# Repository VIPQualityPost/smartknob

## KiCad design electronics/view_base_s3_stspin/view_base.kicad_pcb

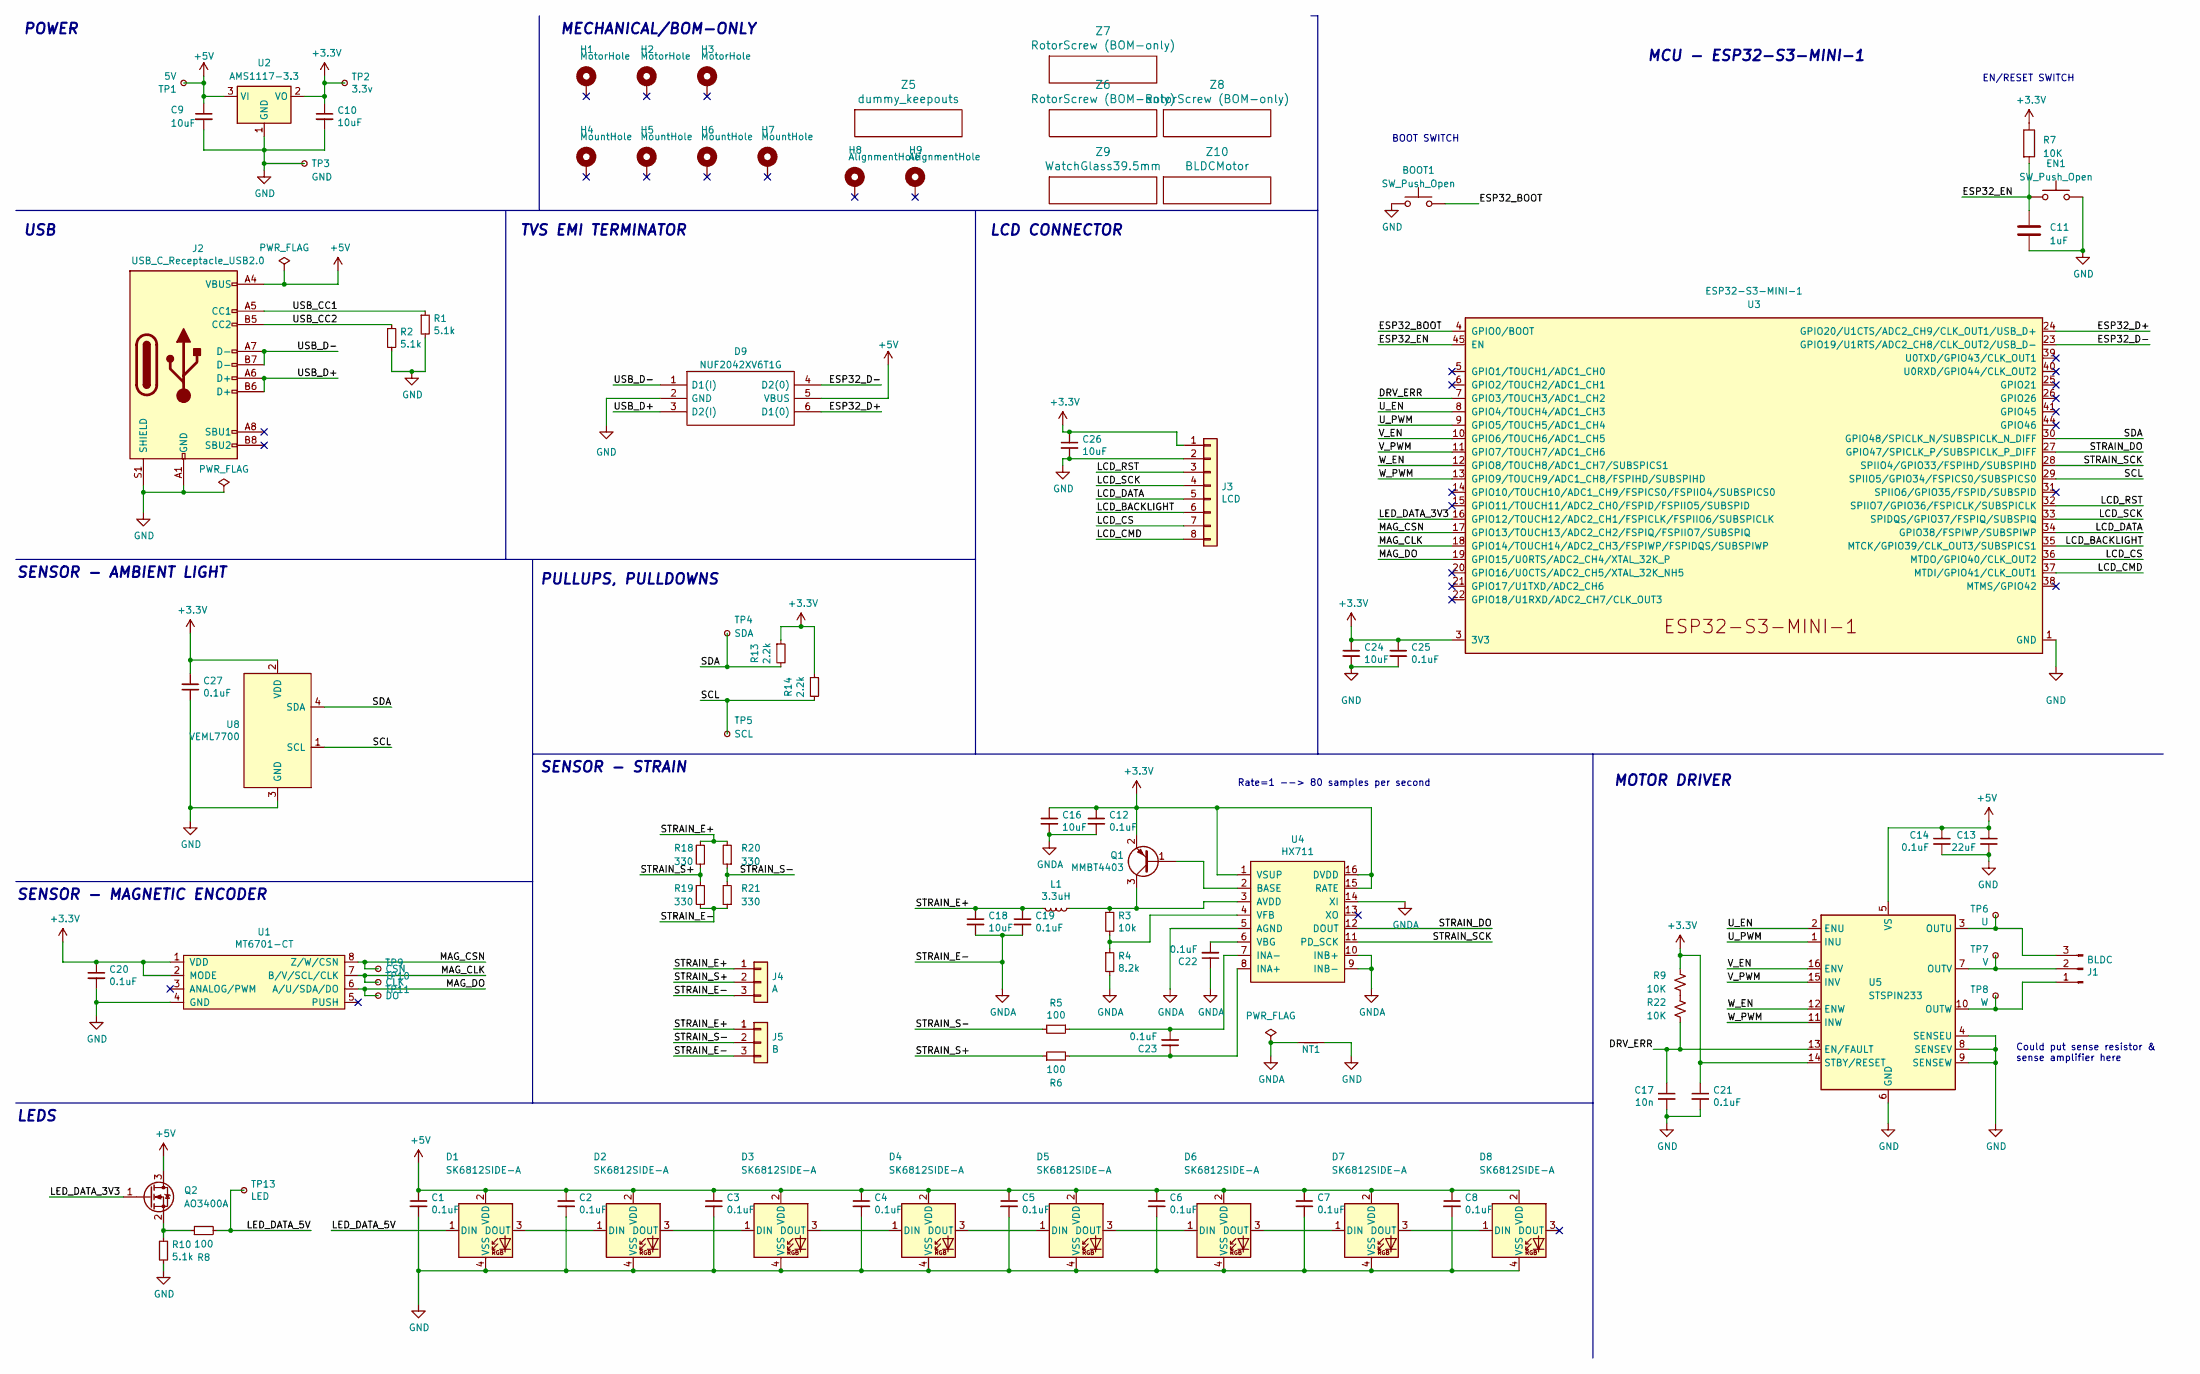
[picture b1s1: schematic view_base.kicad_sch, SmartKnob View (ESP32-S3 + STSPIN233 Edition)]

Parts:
BOOT1: SW_Push_Open; SW_Push_SPST_NO_Alps_SKRK
C1, C2, C3, C4, C5, C6, C7, C8, C12, C14, C19, C20, C21, C22, C23, C25, C27: 0.1uF; C_0603_1608Metric; LCSC C1591
C9, C10, C16, C18, C24, C26: 10uF; C_0805_2012Metric; LCSC C2922480
C11: 1uF; C_0603_1608Metric
C13: 22uF; C_0805_2012Metric; LCSC C98190
C17: 10n; C_0603_1608Metric; LCSC C1591
D1, D2, D3, D4, D5, D6, D7, D8: SK6812SIDE-A; SK6812-SIDE-A; Digikey 1528-4691-ND
D9: NUF2042XV6T1G; SOT-563; Mouser Part Number 863-NUF2042XV6T1G
EN1: SW_Push_Open; SW_Push_SPST_NO_Alps_SKRK
H1, H2, H3: MotorHole; MountingHole_M1.6; LCSC C2931389
H4, H5, H6, H7: MountHole; MountingHole_2.2mm_M2_ISO7380_Pad_NonVirtual; LCSC C2911210 or C2911532 (screw), C2961595 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
H8, H9: AlignmentHole; MountingHole_2.2mm_M2_ISO7380_Pad_NonVirtual
J1: BLDC; 532610371; LCSC C293630
J2: USB_C_Receptacle_USB2.0; USB4510_NoPaste; LCSC C428463
J3: LCD; SolderPads_2mm_8
J4: A; SolderPads_2mm_3_STRAIN
J5: B; SolderPads_2mm_3_STRAIN
L1: 3.3uH; L_0805_2012Metric; LCSC C307744
NT1: NetTie_2; NetTie-2_SMD_Pad0.5mm
Q1: MMBT4403; SOT-23; LCSC C78864
Q2: AO3400A; SOT-23
R1, R2, R10: 5.1k; R_0603_1608Metric; LCSC C105580
R3: 10k; R_0603_1608Metric; LCSC C98220
R4: 8.2k; R_0603_1608Metric; LCSC C114637
R5, R6, R8: 100; R_0603_1608Metric; LCSC C319953
R7, R9, R22: 10K; R_0603_1608Metric
R13, R14: 2.2k; R_0603_1608Metric; LCSC C4190
R18, R19, R20, R21: 330; R_2512_6332Metric; LCSC C19866
TP1: 5V; TestPoint_Pad_D2.0mm_ValueSilk
TP2: 3.3v; TestPoint_Pad_D2.0mm_ValueSilk
TP3: GND; TestPoint_Pad_D2.0mm_ValueSilk
TP4: SDA; TestPoint_Pad_D2.0mm_ValueSilk
TP5: SCL; TestPoint_Pad_D2.0mm_ValueSilk
TP6: U; TestPoint_Pad_D2.0mm_ValueSilk
TP7: V; TestPoint_Pad_D2.0mm_ValueSilk
TP8: W; TestPoint_Pad_D2.0mm_ValueSilk
TP9: CSN; TestPoint_Pad_D2.0mm_ValueSilk
TP10: CLK; TestPoint_Pad_D2.0mm_ValueSilk
TP11: DO; TestPoint_Pad_D2.0mm_ValueSilk
TP13: LED; TestPoint_Pad_D2.0mm_ValueSilk
U1: MT6701-CT; SOIC-8_3.9x4.9mm_P1.27mm; LCSC C2856764, or C3003196
U2: AMS1117-3.3; SOT-223-3_TabPin2; LCSC C5120765
U3: ESP32-S3-MINI-1
U4: HX711; SOIC-16_3.9x9.9mm_P1.27mm; LCSC C43656
U5: STSPIN233; VQFN-16-1EP_3x3mm_P0.5mm_EP1.8x1.8mm
U8: VEML7700; VEML7700-TOP; Digikey VEML7700-TT
Z5: dummy_keepouts; ViewKeepouts3d
Z6, Z7, Z8: RotorScrew (BOM-only); bom_only_no_pin
Z9: WatchGlass39.5mm; bom_only_no_pin
Z10: BLDCMotor; bom_only_no_pin

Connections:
+3V3: C10.1, C12.1, C16.1, C20.1, C21.1, C24.1, C25.1, C26.1, C27.1, J3.1, Q1.2 (E), R7.1, R9.1, R13.1, R14.1, TP2.1, U1.1 (VDD), U1.2 (MODE), U2.2 (VO), U3.3 (3V3), U4.1 (VSUP), U4.15 (RATE), U4.16 (DVDD), U5.14 (STBY/RESET), U8.2 (VDD)
+5V: C1.1, C2.1, C3.1, C4.1, C5.1, C6.1, C7.1, C8.1, C9.1, C13.1, C14.1, D1.2 (VDD), D2.2 (VDD), D3.2 (VDD), D4.2 (VDD), D5.2 (VDD), D6.2 (VDD), D7.2 (VDD), D8.2 (VDD), D9.5 (VBUS), J2.A4 (VBUS), J2.A9 (VBUS), J2.B4 (VBUS), J2.B9 (VBUS), Q2.3 (D), TP1.1, U2.3 (VI), U5.5 (VS)
/DRV_ERR: C17.1, R22.2, U3.7 (GPIO3/TOUCH3/ADC1_CH2), U5.13 (EN/FAULT)
/ESP32_BOOT: BOOT1.2, U3.4 (GPIO0/BOOT); also elsewhere on the board
/ESP32_D+: D9.6 (D1(0)), U3.24 (GPIO20/U1CTS/ADC2_CH9/CLK_OUT1/USB_D+)
/ESP32_D-: D9.4 (D2(0)), U3.23 (GPIO19/U1RTS/ADC2_CH8/CLK_OUT2/USB_D-)
/ESP32_EN: C11.1, EN1.1, R7.2, U3.45 (EN); also elsewhere on the board
/LCD_BACKLIGHT: J3.6, U3.35 (MTCK/GPIO39/CLK_OUT3/SUBSPICS1)
/LCD_CMD: J3.8, U3.37 (MTDI/GPIO41/CLK_OUT1)
/LCD_CS: J3.7, U3.36 (MTDO/GPIO40/CLK_OUT2)
/LCD_DATA: J3.5, U3.34 (GPIO38/FSPIWP/SUBSPIWP)
/LCD_RST: J3.3, U3.32 (SPIIO7/GPIO36/FSPICLK/SUBSPICLK)
/LCD_SCK: J3.4, U3.33 (SPIDQS/GPIO37/FSPIQ/SUBSPIQ)
/LED_DATA_3V3: Q2.1 (G), U3.16 (GPIO12/TOUCH12/ADC2_CH1/FSPICLK/FSPIIO6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)
/LED_DATA_5V: D1.1 (DIN), R8.2, TP13.1
/MAG_CLK: TP10.1, U1.7 (B/V/SCL/CLK), U3.18 (GPIO14/TOUCH14/ADC2_CH3/FSPIWP/FSPIDQS/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)
/MAG_CSN: TP9.1, U1.8 (Z/W/CSN), U3.17 (GPIO13/TOUCH13/ADC2_CH2/FSPIQ/FSPIIO7/S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)
/MAG_DO: TP11.1, U1.6 (A/U/SDA/DO), U3.19 (GPIO15/U0RTS/ADC2_CH4/XTAL_32K_P)
/SCL: R14.2, TP5.1, U3.29 (SPIIO5/GPIO34/FSPICS0/SUBSPICS0), U8.1 (SCL)
/SDA: R13.2, TP4.1, U3.30 (GPIO48/SPICLK_N/SUBSPICLK_N_DIFF), U8.4 (SDA)
/STRAIN_DO: U3.27 (GPIO47/SPICLK_P/SUBSPICLK_P_DIFF), U4.12 (DOUT)
/STRAIN_E+: C18.1, C19.1, J4.1, J5.1, L1.2, R18.1, R20.2
/STRAIN_S+: J4.2, R6.1, R18.2, R19.1
/STRAIN_S-: J5.2, R5.2, R20.1, R21.2
/STRAIN_SCK: U3.28 (SPIIO4/GPIO33/FSPIHD/SUBSPIHD), U4.11 (PD_SCK)
/USB_CC1: J2.A5 (CC1), R1.1
/USB_CC2: J2.B5 (CC2), R2.1
/USB_D+: D9.3 (D2(I)), J2.A6 (D+), J2.B6 (D+)
/USB_D-: D9.1 (D1(I)), J2.A7 (D-), J2.B7 (D-)
/U_EN: U3.8 (GPIO4/TOUCH4/ADC1_CH3), U5.2 (ENU); also elsewhere on the board
/U_PWM: U3.9 (GPIO5/TOUCH5/ADC1_CH4), U5.1 (INU); also elsewhere on the board
/V_EN: U3.10 (GPIO6/TOUCH6/ADC1_CH5), U5.16 (ENV); also elsewhere on the board
/V_PWM: U3.11 (GPIO7/TOUCH7/ADC1_CH6), U5.15 (INV); also elsewhere on the board
/W_EN: U3.12 (GPIO8/TOUCH8/ADC1_CH7/SUBSPICS1), U5.12 (ENW); also elsewhere on the board
/W_PWM: U3.13 (GPIO9/TOUCH9/ADC1_CH8/FSPIHD/SUBSPIHD), U5.11 (INW); also elsewhere on the board
GND: BOOT1.1, C1.2, C2.2, C3.2, C4.2, C5.2, C6.2, C7.2, C8.2, C9.2, C10.2, C11.2, C13.2, C14.2, C17.2, C20.2, C21.2, C24.2, C25.2, C26.2, C27.2, D1.4 (VSS), D2.4 (VSS), D3.4 (VSS), D4.4 (VSS), D5.4 (VSS), D6.4 (VSS), D7.4 (VSS), D8.4 (VSS), D9.2 (GND), EN1.2, J2.A1 (GND), J2.A12 (GND), J2.B1 (GND), J2.B12 (GND), J2.S1 (SHIELD), J3.2, NT1.2, R1.2, R2.2, R10.2, TP3.1, U1.4 (GND), U2.1 (GND), U3.1 (GND), U3.2 (GND), U3.42 (GND), U3.43 (GND), U3.46 (GND), U3.47 (GND), U3.48 (GND), U3.49 (GND), U3.50 (GND), U3.51 (GND), U3.52 (GND), U3.53 (GND), U3.54 (GND), U3.55 (GND), U3.56 (GND), U3.57 (GND), U3.58 (GND), U3.59 (GND), U3.60 (GND), U3.61 (GND), U3.62 (GND), U3.63 (GND), U3.64 (GND), U3.65 (GND), U5.4 (SENSEU), U5.6 (GND), U5.8 (SENSEV), U5.9 (SENSEW), U5.17 (GND), U8.3 (GND); also elsewhere on the board
GNDA: C12.2, C16.2, C18.2, C19.2, C22.1, J4.3, J5.3, NT1.1, R4.2, R19.2, R21.1, U4.5 (AGND), U4.9 (INB-), U4.10 (INB+), U4.14 (XI)
unnamed: D1.3 (DOUT), D2.1 (DIN)
unnamed: D2.3 (DOUT), D3.1 (DIN)
unnamed: D3.3 (DOUT), D4.1 (DIN)
unnamed: D4.3 (DOUT), D5.1 (DIN)
unnamed: D5.3 (DOUT), D6.1 (DIN)
unnamed: D6.3 (DOUT), D7.1 (DIN)
unnamed: D7.3 (DOUT), D8.1 (DIN)
unnamed: J1.1, TP8.1, U5.10 (OUTW)
unnamed: J1.2, TP7.1, U5.7 (OUTV)
unnamed: J1.3, TP6.1, U5.3 (OUTU)
unnamed: Q1.1 (B), U4.2 (BASE)
unnamed: L1.1, Q1.3 (C), R3.1, U4.3 (AVDD)
unnamed: Q2.2 (S), R8.1, R10.1
unnamed: R9.2, R22.1
unnamed: C23.1, R6.2, U4.8 (INA+)
unnamed: C23.2, R5.1, U4.7 (INA-)
unnamed: C22.2, U4.6 (VBG)
unnamed: R3.2, R4.1, U4.4 (VFB)

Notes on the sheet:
POWER
Could put sense resistor & sense amplifier here
MCU - ESP32-S3-MINI-1
SENSOR - MAGNETIC ENCODER
MOTOR DRIVER
MECHANICAL/BOM-ONLY
TVS EMI TERMINATOR
Rate=1 --> 80 samples per second
EN/RESET SWITCH
SENSOR - AMBIENT LIGHT
BOOT SWITCH
USB
SENSOR - STRAIN
LEDS
PULLUPS, PULLDOWNS
LCD CONNECTOR

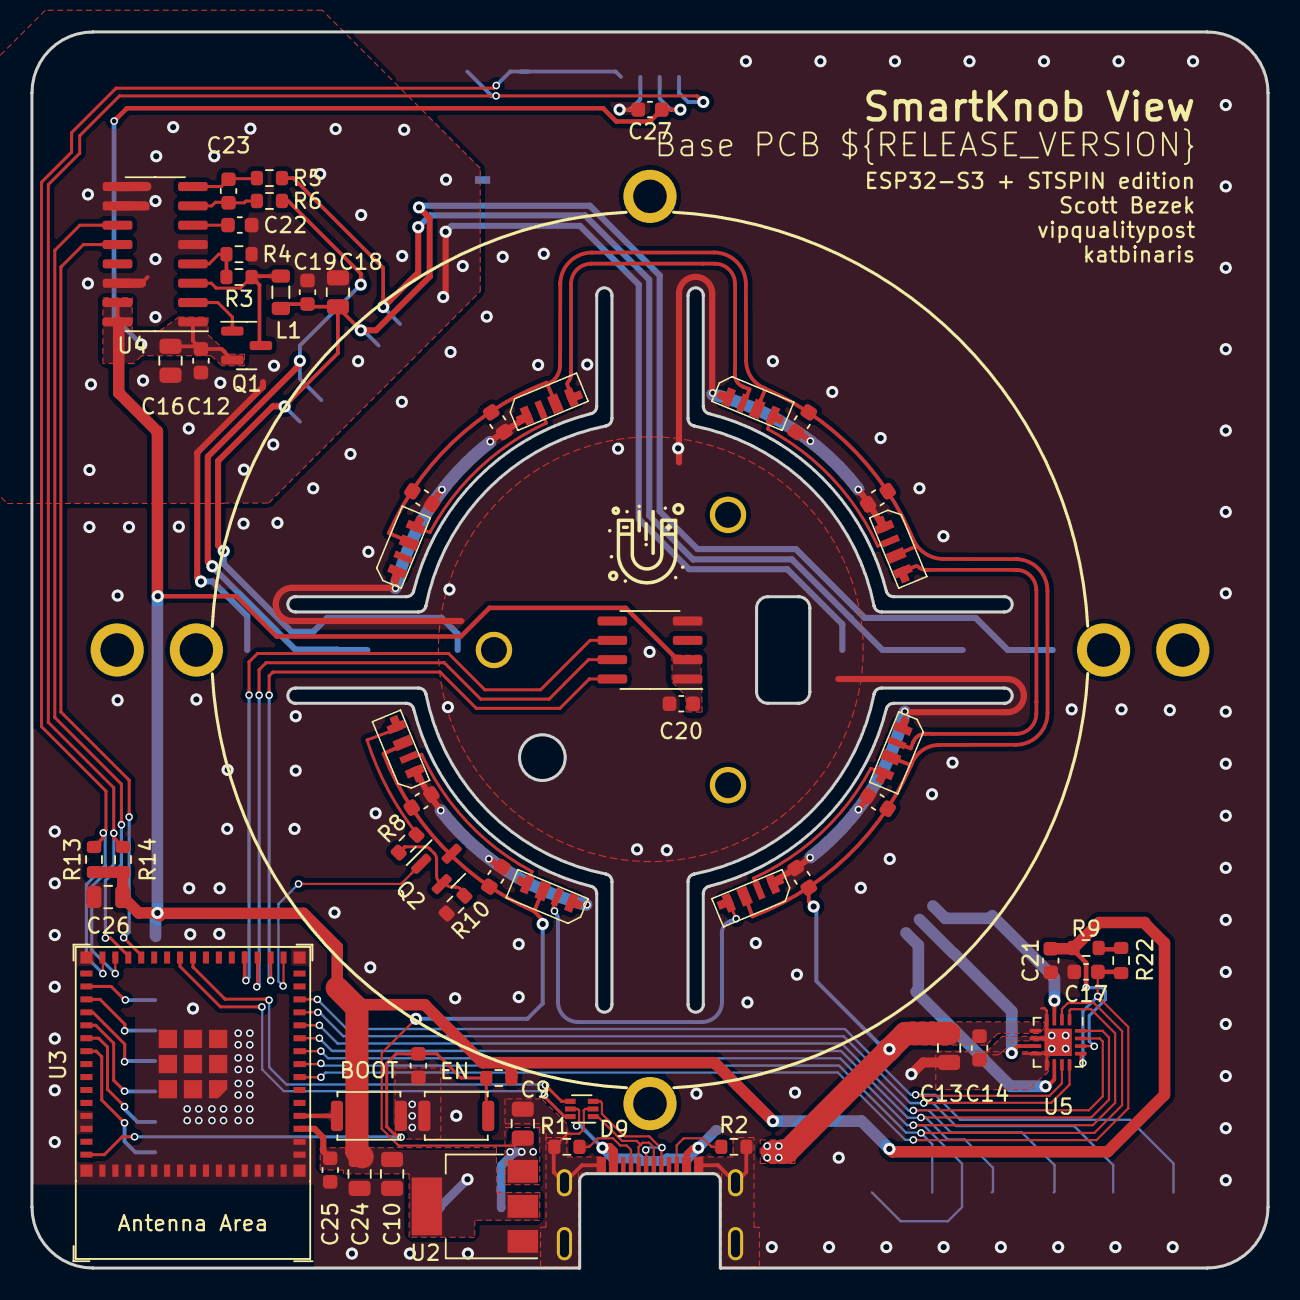
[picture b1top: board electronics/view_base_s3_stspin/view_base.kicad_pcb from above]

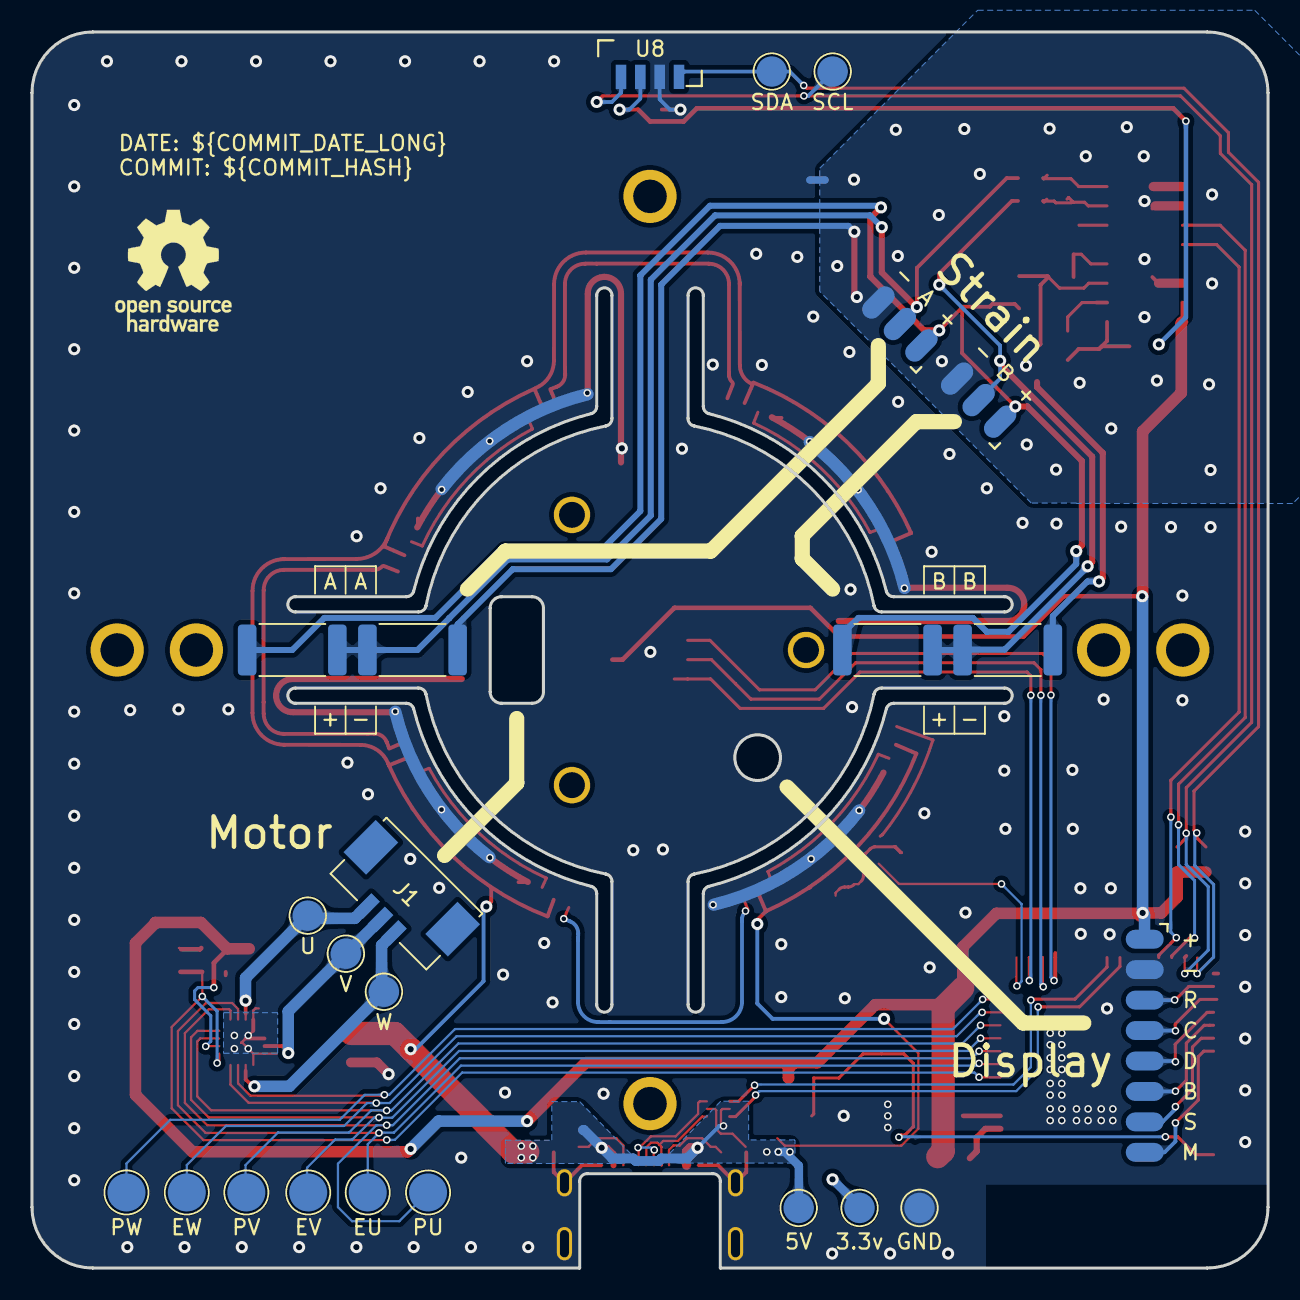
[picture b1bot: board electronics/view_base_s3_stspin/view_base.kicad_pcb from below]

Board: 2 copper layers, 81.2 x 81.2 mm, 98 parts (24 on the bottom side), 55 nets.

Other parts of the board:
BOOT: SW_Push_Open; SW_Push_SPST_NO_Alps_SKRK
EN: SW_Push_Open; SW_Push_SPST_NO_Alps_SKRK
EU: TestPoint_Pad_D2.5mm
EV: TestPoint_Pad_D2.5mm
EW: TestPoint_Pad_D2.5mm
PU: TestPoint_Pad_D2.5mm
PV: TestPoint_Pad_D2.5mm
PW: TestPoint_Pad_D2.5mm

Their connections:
/ESP32_BOOT: BOOT.2; also elsewhere on the board
/ESP32_EN: EN.1; also elsewhere on the board
/U_EN: EU.1; also elsewhere on the board
/U_PWM: PU.1; also elsewhere on the board
/V_EN: EV.1; also elsewhere on the board
/V_PWM: PV.1; also elsewhere on the board
/W_EN: EW.1; also elsewhere on the board
/W_PWM: PW.1; also elsewhere on the board
GND: BOOT.1, EN.2; also elsewhere on the board

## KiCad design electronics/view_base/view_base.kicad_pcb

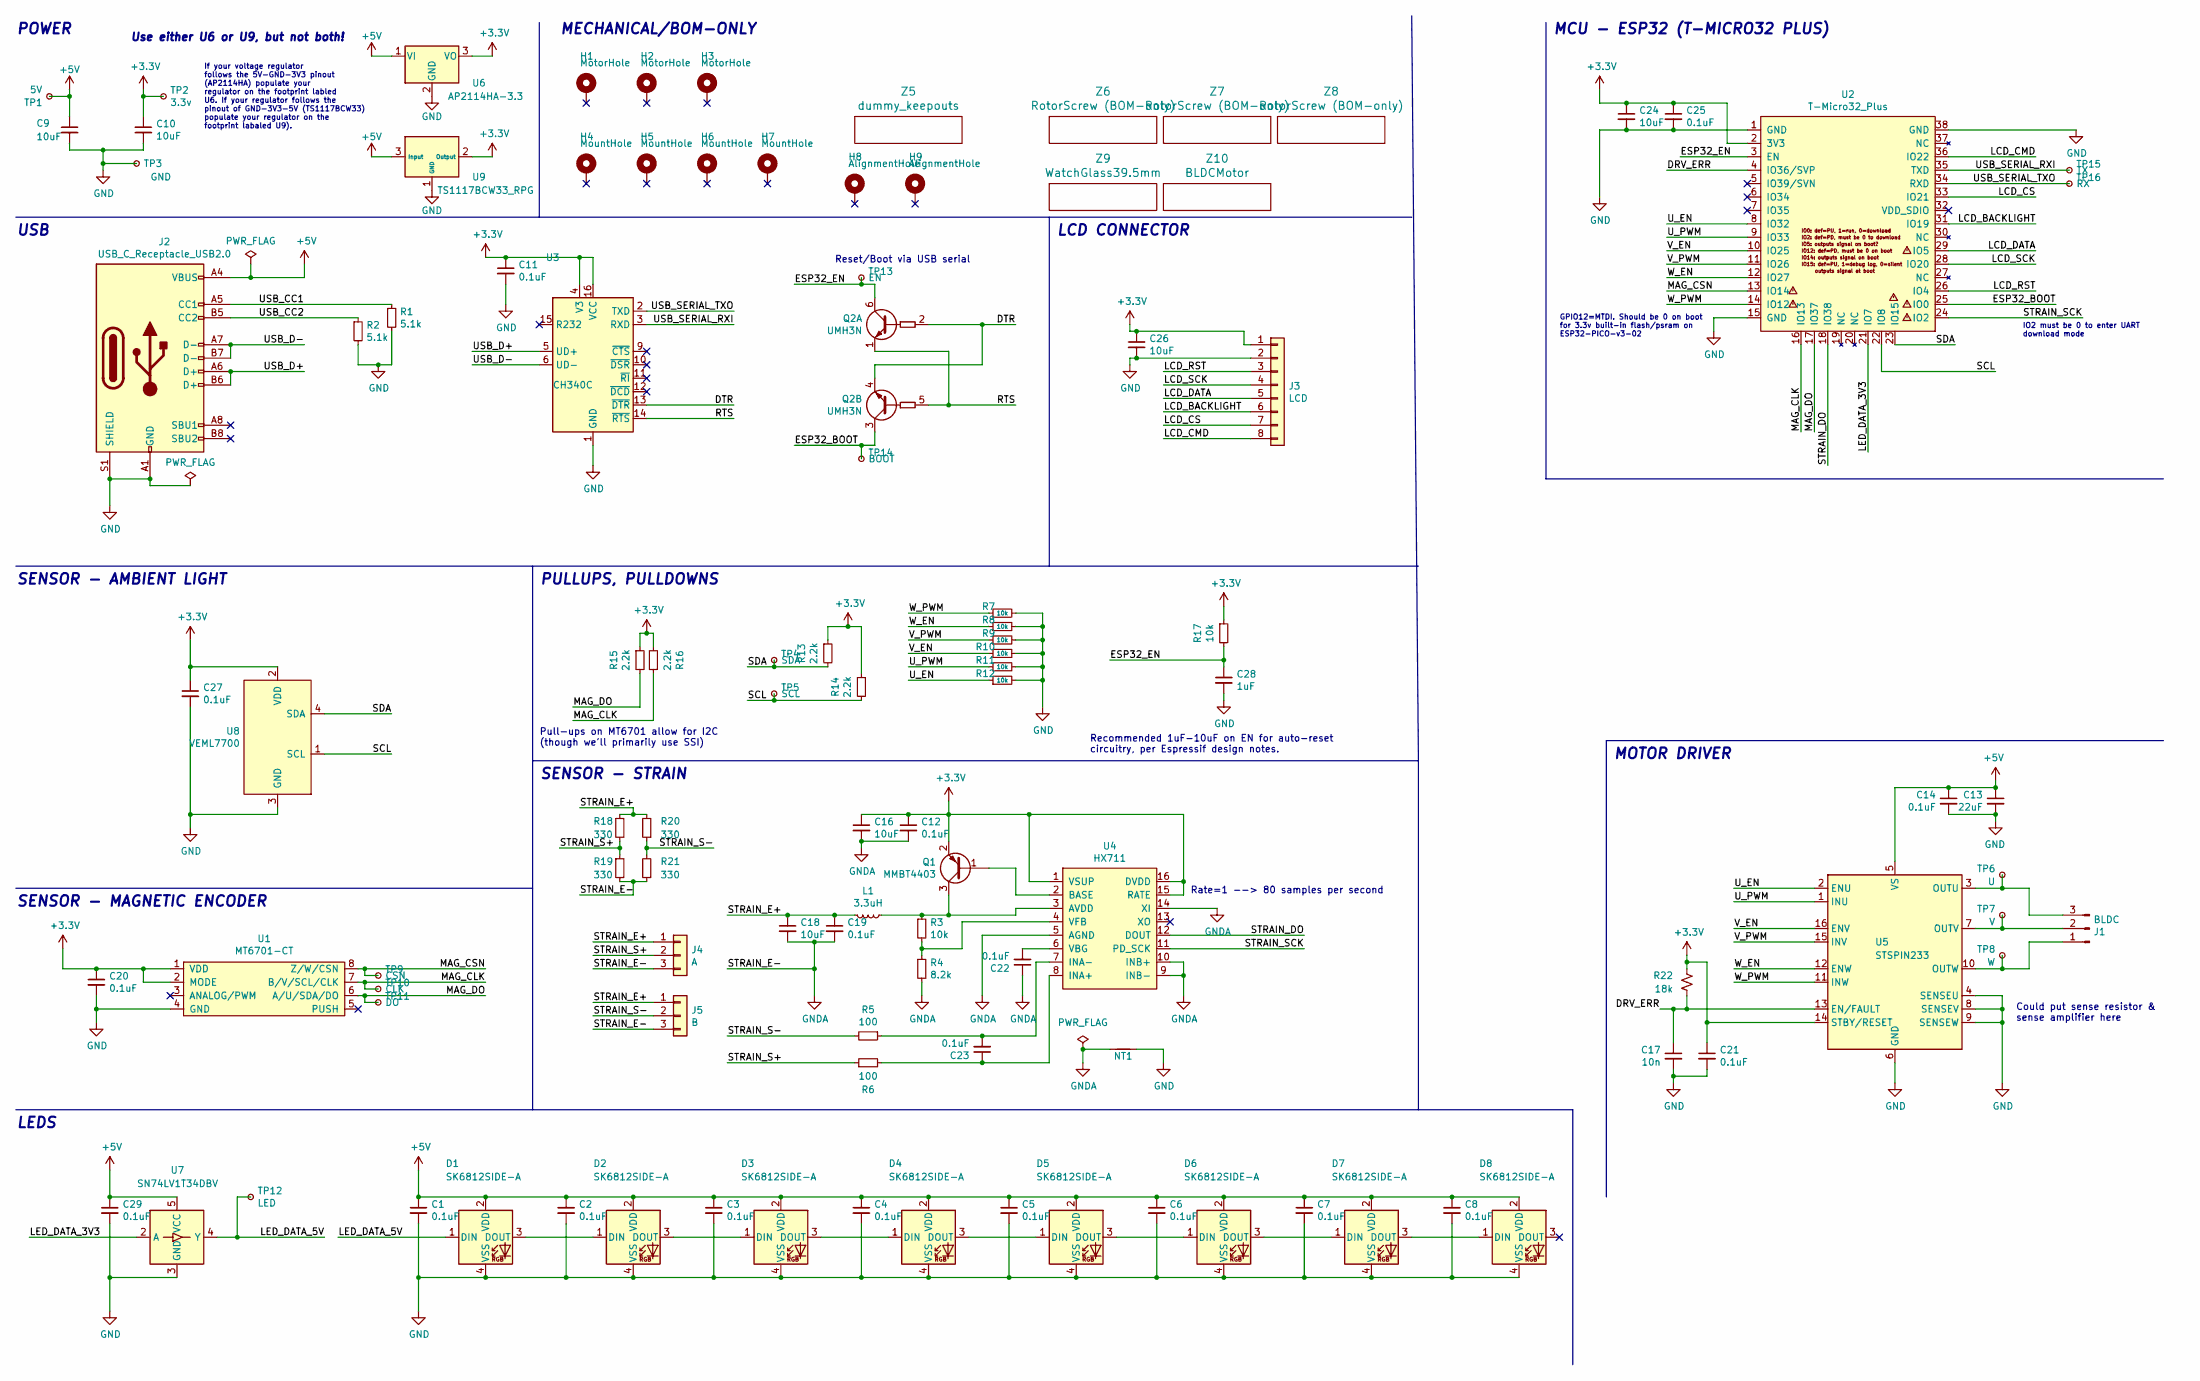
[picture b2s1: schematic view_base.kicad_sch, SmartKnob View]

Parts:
C1, C2, C3, C4, C5, C6, C7, C8, C11, C12, C14, C19, C20, C21, C22, C23, C25, C27, C29: 0.1uF; C_0603_1608Metric; LCSC C1591
C9, C10, C16, C18, C24, C26: 10uF; C_0805_2012Metric; LCSC C2922480
C13: 22uF; C_0805_2012Metric; LCSC C98190
C17: 10n; C_0603_1608Metric; LCSC C1591
C28: 1uF; C_0603_1608Metric; Mouser 187-CL10A105KA8NNNC
D1, D2, D3, D4, D5, D6, D7, D8: SK6812SIDE-A; SK6812-SIDE-A; Digikey 1528-4691-ND
H1, H2, H3: MotorHole; MountingHole_M1.6; LCSC C2931389
H4, H5, H6, H7: MountHole; MountingHole_2.2mm_M2_ISO7380_Pad_NonVirtual; LCSC C2911210 or C2911532 (screw), C2961595 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
H8, H9: AlignmentHole; MountingHole_2.2mm_M2_ISO7380_Pad_NonVirtual
J1: BLDC; 532610371; LCSC C293630
J2: USB_C_Receptacle_USB2.0; USB4510_NoPaste; LCSC C428463
J3: LCD; SolderPads_2mm_8
J4: A; SolderPads_2mm_3_STRAIN
J5: B; SolderPads_2mm_3_STRAIN
L1: 3.3uH; L_0805_2012Metric; LCSC C307744
NT1: NetTie_2; NetTie-2_SMD_Pad0.5mm
Q1: MMBT4403; SOT-23; LCSC C78864
Q2: UMH3N; SOT-363_SC-70-6; LCSC C62892
R1, R2: 5.1k; R_0603_1608Metric; LCSC C105580
R3, R7, R8, R9, R10, R11, R12, R17: 10k; R_0603_1608Metric; LCSC C98220
R4: 8.2k; R_0603_1608Metric; LCSC C114637
R5, R6: 100; R_0603_1608Metric; LCSC C319953
R13, R14, R15, R16: 2.2k; R_0603_1608Metric; LCSC C4190
R18, R19, R20, R21: 330; R_2512_6332Metric; LCSC C19866
R22: 18k; R_0603_1608Metric
TP1: 5V; TestPoint_Pad_D2.0mm_ValueSilk
TP2: 3.3v; TestPoint_Pad_D2.0mm_ValueSilk
TP3: GND; TestPoint_Pad_D2.0mm_ValueSilk
TP4: SDA; TestPoint_Pad_D2.0mm_ValueSilk
TP5: SCL; TestPoint_Pad_D2.0mm_ValueSilk
TP6: U; TestPoint_Pad_D2.0mm_ValueSilk
TP7: V; TestPoint_Pad_D2.0mm_ValueSilk
TP8: W; TestPoint_Pad_D2.0mm_ValueSilk
TP9: CSN; TestPoint_Pad_D2.0mm_ValueSilk
TP10: CLK; TestPoint_Pad_D2.0mm_ValueSilk
TP11: DO; TestPoint_Pad_D2.0mm_ValueSilk
TP12: LED; TestPoint_Pad_D2.0mm_ValueSilk
TP13: EN; TestPoint_Pad_D2.0mm_ValueSilk
TP14: BOOT; TestPoint_Pad_D2.0mm_ValueSilk
TP15: TX; TestPoint_Pad_D2.0mm_ValueSilk
TP16: RX; TestPoint_Pad_D2.0mm_ValueSilk
U1: MT6701-CT; SOIC-8_3.9x4.9mm_P1.27mm; LCSC C2856764, or C3003196
U2: T-Micro32_Plus; T-Micro32; Digikey N/A
U3: CH340C; SOIC-16_3.9x9.9mm_P1.27mm; LCSC C84681
U4: HX711; SOIC-16_3.9x9.9mm_P1.27mm; LCSC C43656
U5: STSPIN233; VQFN-16-1EP_3x3mm_P0.5mm_EP1.8x1.8mm
U6: AP2114HA-3.3; SOT-223-3_TabPin2_InGndOut; LCSC C460314
U7: SN74LV1T34DBV; SOT-23-5; LCSC C100024
U8: VEML7700; VEML7700-TOP; Digikey VEML7700-TT
U9: TS1117BCW33_RPG; SOT-223-3_TabPin2_GndOutIn; LCSC C6186, C35879, or others
Z5: dummy_keepouts; ViewKeepouts3d
Z6, Z7, Z8: RotorScrew (BOM-only); bom_only_no_pin
Z9: WatchGlass39.5mm; bom_only_no_pin
Z10: BLDCMotor; bom_only_no_pin

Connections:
+3V3: C10.1, C11.1, C12.1, C16.1, C20.1, C21.1, C24.1, C25.1, C26.1, C27.1, J3.1, Q1.2 (E), R13.1, R14.1, R15.1, R16.2, R17.1, R22.1, TP2.1, U1.1 (VDD), U1.2 (MODE), U2.2 (3V3), U3.4 (V3), U3.16 (VCC), U4.1 (VSUP), U4.15 (RATE), U4.16 (DVDD), U5.14 (STBY/RESET), U6.3 (VO), U8.2 (VDD), U9.2 (Output)
+5V: C1.1, C2.1, C3.1, C4.1, C5.1, C6.1, C7.1, C8.1, C9.1, C13.1, C14.1, C29.1, D1.2 (VDD), D2.2 (VDD), D3.2 (VDD), D4.2 (VDD), D5.2 (VDD), D6.2 (VDD), D7.2 (VDD), D8.2 (VDD), J2.A4 (VBUS), J2.A9 (VBUS), J2.B4 (VBUS), J2.B9 (VBUS), TP1.1, U5.5 (VS), U6.1 (VI), U7.5 (VCC), U9.3 (Input)
/DRV_ERR: C17.1, R22.2, U2.4 (IO36/SVP), U5.13 (EN/FAULT)
/DTR: Q2.2 (B1), Q2.4 (E2), U3.13 (~DTR)
/ESP32_BOOT: Q2.3 (C2), TP14.1, U2.25 (IO0)
/ESP32_EN: C28.1, Q2.6 (C1), R17.2, TP13.1, U2.3 (EN)
/LCD_BACKLIGHT: J3.6, U2.31 (IO19)
/LCD_CMD: J3.8, U2.36 (IO22)
/LCD_CS: J3.7, U2.33 (IO21)
/LCD_DATA: J3.5, U2.29 (IO5)
/LCD_RST: J3.3, U2.26 (IO4)
/LCD_SCK: J3.4, U2.28 (IO20)
/LED_DATA_3V3: U2.21 (IO7), U7.2 (A)
/LED_DATA_5V: D1.1 (DIN), TP12.1, U7.4 (Y)
/MAG_CLK: R16.1, TP10.1, U1.7 (B/V/SCL/CLK), U2.16 (IO13)
/MAG_CSN: TP9.1, U1.8 (Z/W/CSN), U2.13 (IO14)
/MAG_DO: R15.2, TP11.1, U1.6 (A/U/SDA/DO), U2.17 (IO37)
/RTS: Q2.1 (E1), Q2.5 (B2), U3.14 (~RTS)
/SCL: R14.2, TP5.1, U2.22 (IO8), U8.1 (SCL)
/SDA: R13.2, TP4.1, U2.23 (IO15), U8.4 (SDA)
/STRAIN_DO: U2.18 (IO38), U4.12 (DOUT)
/STRAIN_E+: C18.1, C19.1, J4.1, J5.1, L1.2, R18.1, R20.2
/STRAIN_S+: J4.2, R6.1, R18.2, R19.1
/STRAIN_S-: J5.2, R5.2, R20.1, R21.2
/STRAIN_SCK: U2.24 (IO2), U4.11 (PD_SCK)
/USB_CC1: J2.A5 (CC1), R1.1
/USB_CC2: J2.B5 (CC2), R2.1
/USB_D+: J2.A6 (D+), J2.B6 (D+), U3.5 (UD+)
/USB_D-: J2.A7 (D-), J2.B7 (D-), U3.6 (UD-)
/USB_SERIAL_RXI: TP15.1, U2.35 (TXD), U3.3 (RXD)
/USB_SERIAL_TXO: TP16.1, U2.34 (RXD), U3.2 (TXD)
/U_EN: R12.1, U2.8 (IO32), U5.2 (ENU)
/U_PWM: R11.1, U2.9 (IO33), U5.1 (INU)
/V_EN: R10.1, U2.10 (IO25), U5.16 (ENV)
/V_PWM: R9.1, U2.11 (IO26), U5.15 (INV)
/W_EN: R8.1, U2.12 (IO27), U5.12 (ENW)
/W_PWM: R7.1, U2.14 (IO12), U5.11 (INW)
GND: C1.2, C2.2, C3.2, C4.2, C5.2, C6.2, C7.2, C8.2, C9.2, C10.2, C11.2, C13.2, C14.2, C17.2, C20.2, C21.2, C24.2, C25.2, C26.2, C27.2, C28.2, C29.2, D1.4 (VSS), D2.4 (VSS), D3.4 (VSS), D4.4 (VSS), D5.4 (VSS), D6.4 (VSS), D7.4 (VSS), D8.4 (VSS), J2.A1 (GND), J2.A12 (GND), J2.B1 (GND), J2.B12 (GND), J2.S1 (SHIELD), J3.2, NT1.2, R1.2, R2.2, R7.2, R8.2, R9.2, R10.2, R11.2, R12.2, TP3.1, U1.4 (GND), U2.1 (GND), U2.15 (GND), U2.38 (GND), U3.1 (GND), U5.4 (SENSEU), U5.6 (GND), U5.8 (SENSEV), U5.9 (SENSEW), U5.17 (GND), U6.2 (GND), U7.3 (GND), U8.3 (GND), U9.1 (GND)
GNDA: C12.2, C16.2, C18.2, C19.2, C22.1, J4.3, J5.3, NT1.1, R4.2, R19.2, R21.1, U4.5 (AGND), U4.9 (INB-), U4.10 (INB+), U4.14 (XI)
unnamed: D1.3 (DOUT), D2.1 (DIN)
unnamed: D2.3 (DOUT), D3.1 (DIN)
unnamed: D3.3 (DOUT), D4.1 (DIN)
unnamed: D4.3 (DOUT), D5.1 (DIN)
unnamed: D5.3 (DOUT), D6.1 (DIN)
unnamed: D6.3 (DOUT), D7.1 (DIN)
unnamed: D7.3 (DOUT), D8.1 (DIN)
unnamed: J1.1, TP8.1, U5.10 (OUTW)
unnamed: J1.2, TP7.1, U5.7 (OUTV)
unnamed: J1.3, TP6.1, U5.3 (OUTU)
unnamed: Q1.1 (B), U4.2 (BASE)
unnamed: L1.1, Q1.3 (C), R3.1, U4.3 (AVDD)
unnamed: C23.1, R6.2, U4.8 (INA+)
unnamed: C23.2, R5.1, U4.7 (INA-)
unnamed: C22.2, U4.6 (VBG)
unnamed: R3.2, R4.1, U4.4 (VFB)

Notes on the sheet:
POWER
Could put sense resistor & sense amplifier here
MCU - ESP32 (T-MICRO32 PLUS)
If your voltage regulator follows the 5V-GND-3V3 pinout (AP2114HA) populate your regulator on the footprint labled U6. If your regulator follows the pinout of GND-3V3-5V (TS1117BCW33) populate your regulator on the footprint labaled U9).
SENSOR - MAGNETIC ENCODER
MOTOR DRIVER
MECHANICAL/BOM-ONLY
IO2 must be 0 to enter UART download mode
GPIO12=MTDI. Should be 0 on boot for 3.3v built-in flash/psram on ESP32-PICO-v3-02
Pull-ups on MT6701 allow for I2C (though we'll primarily use SSI)
Use either U6 or U9, but not both!
Rate=1 --> 80 samples per second
SENSOR - AMBIENT LIGHT
Recommended 1uF-10uF on EN for auto-reset circuitry, per Espressif design notes.
USB
SENSOR - STRAIN
LEDS
PULLUPS, PULLDOWNS
LCD CONNECTOR
Reset/Boot via USB serial

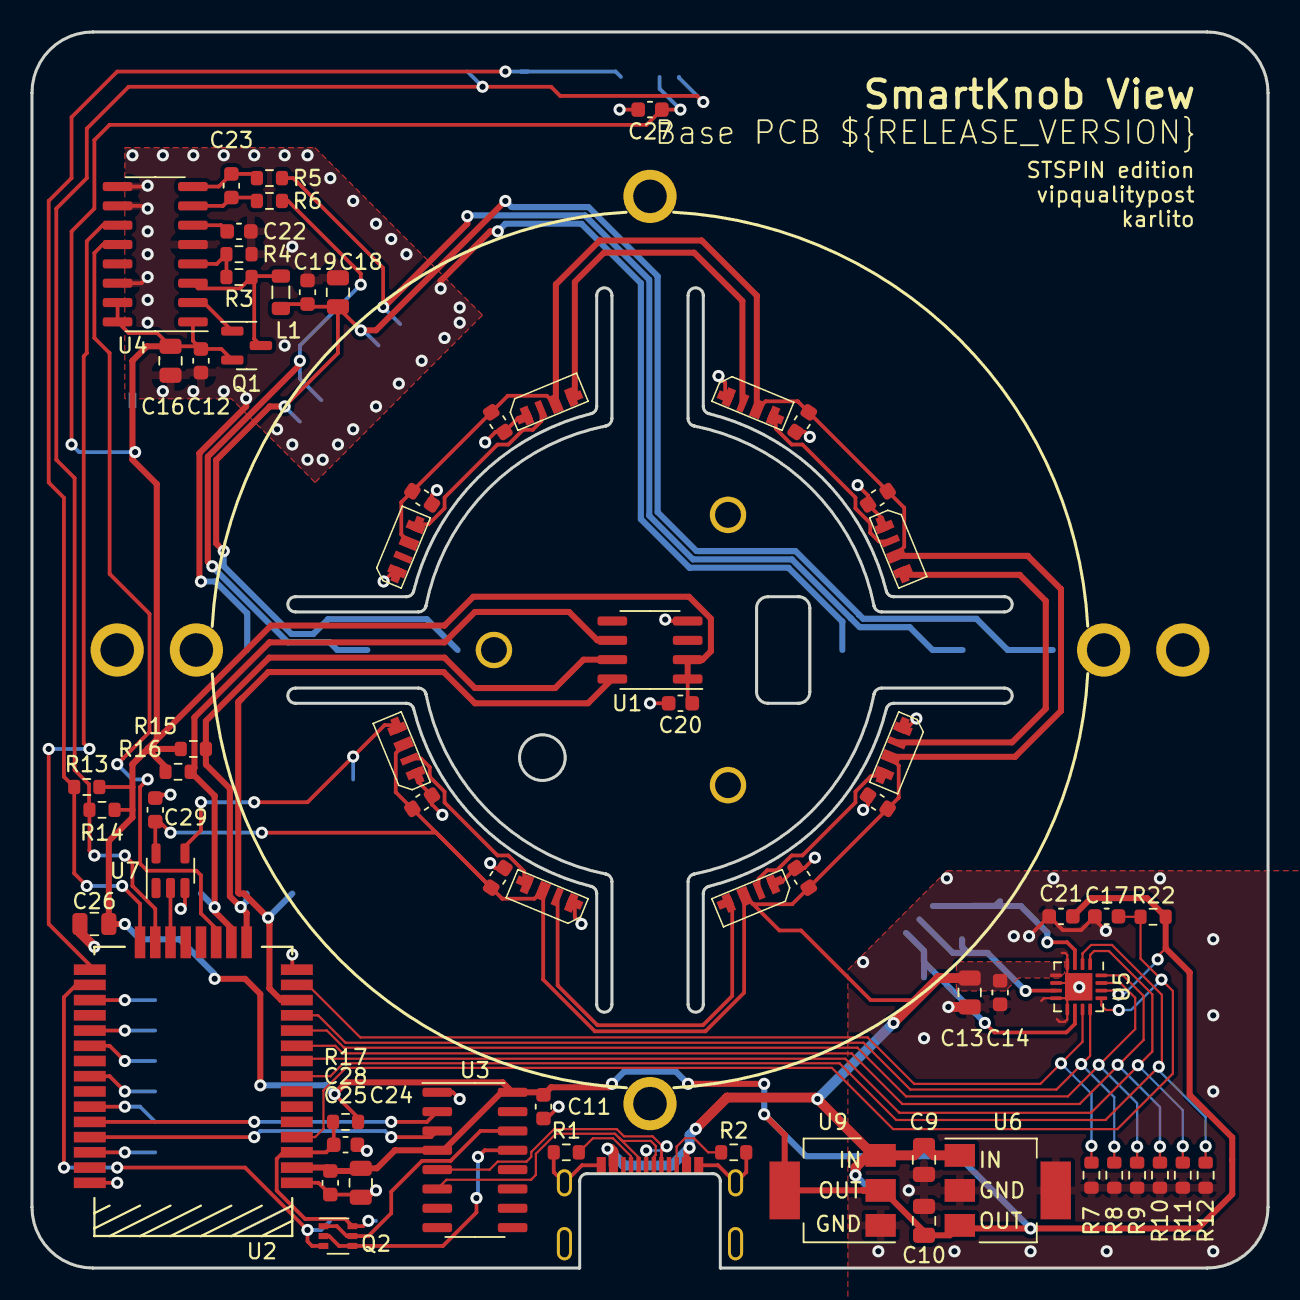
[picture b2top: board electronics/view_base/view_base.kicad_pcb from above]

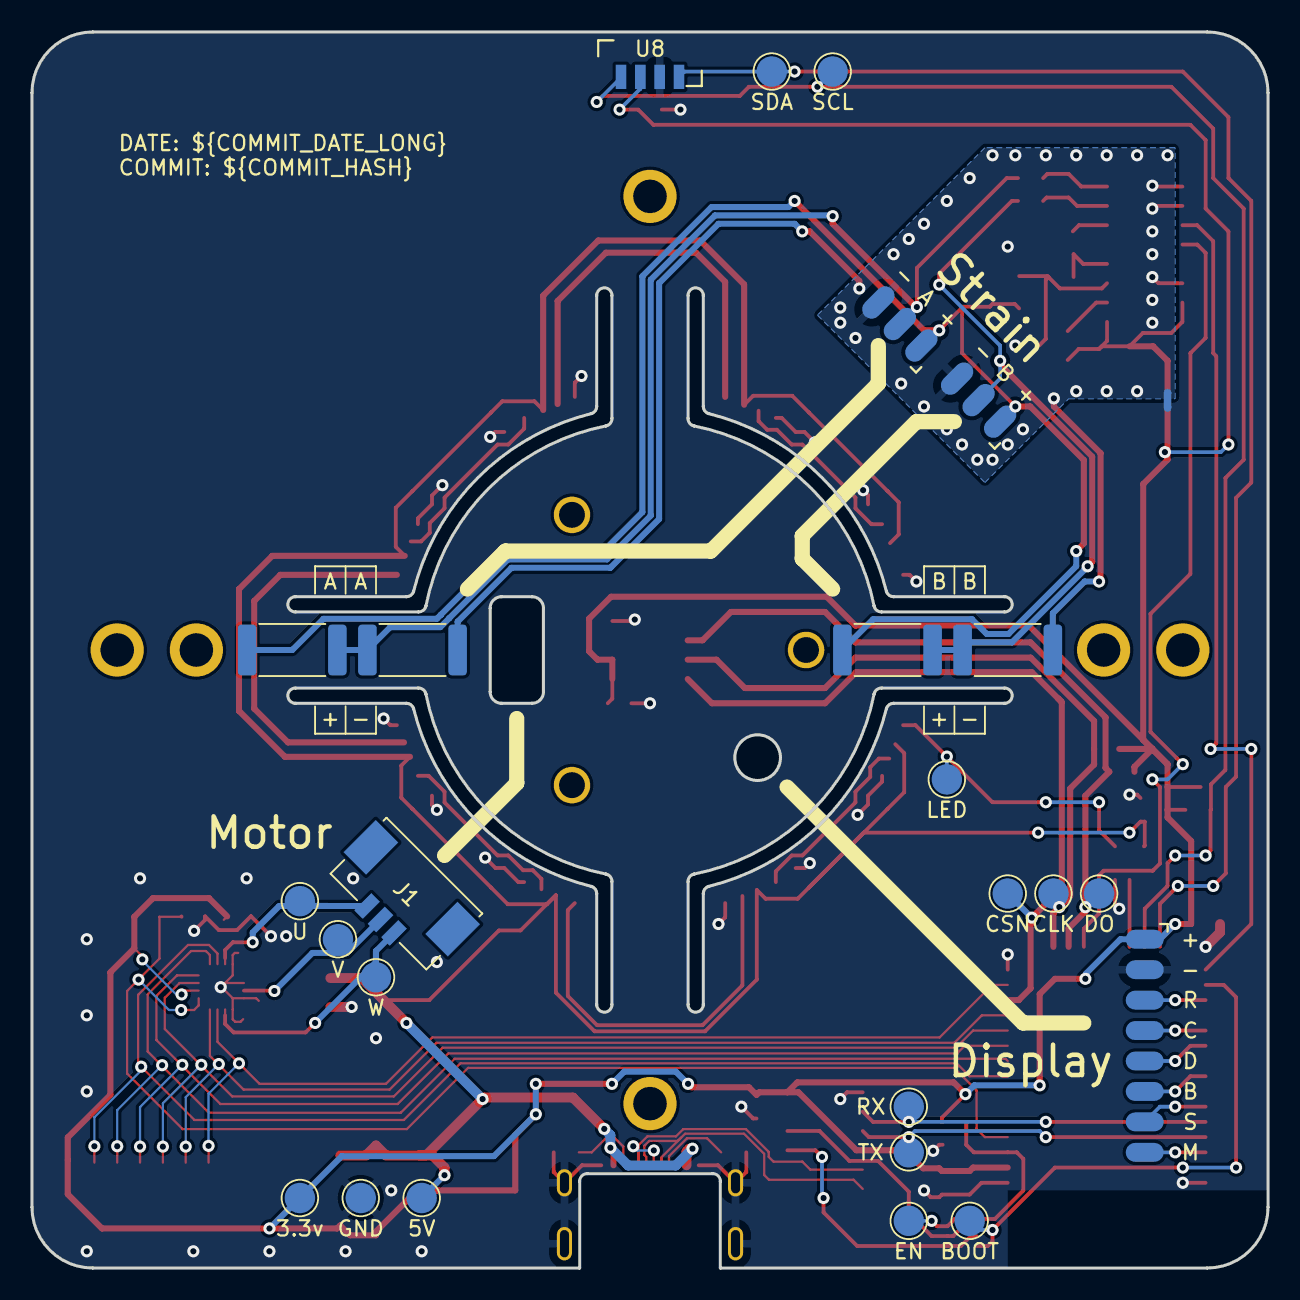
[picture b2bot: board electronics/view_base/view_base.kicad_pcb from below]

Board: 2 copper layers, 81.2 x 81.2 mm, 107 parts (26 on the bottom side), 55 nets.

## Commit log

2023-10-16 change TMC6300 to STSPIN233
2023-10-16 update platformio
2023-10-18 View Base with ESP32-S3 and STSPIN233 variant. Layout Refactor; platofrmio.ini + motor_task.h update.
2023-10-19 Update platformio.ini
    Corrected indent

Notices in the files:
parts and their libraries:
Copyright 2021 Accelerated Designs. All rights reserved.
